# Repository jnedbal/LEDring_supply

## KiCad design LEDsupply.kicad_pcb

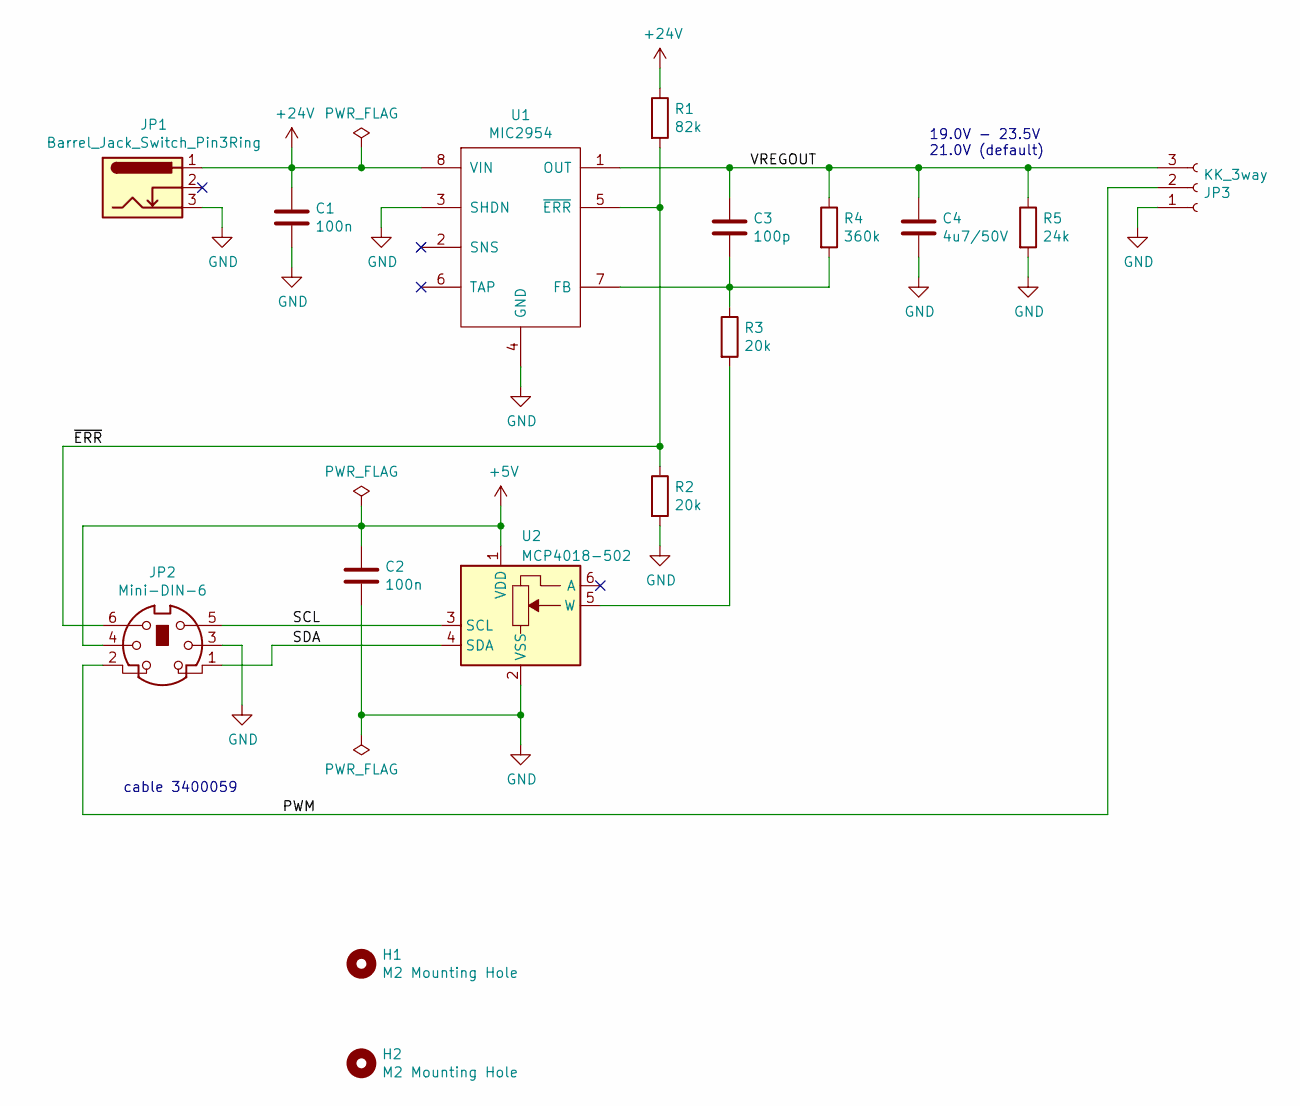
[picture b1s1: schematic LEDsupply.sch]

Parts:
C1, C2: 100n; C_0603_1608Metric; Part Number MC0603B104K500CT
C3: 100p; C_0603_1608Metric; Part Number MC0603B101K500CT
C4: 4u7/50V; C_1206_3216Metric; Part Number GRM31CR71H475KA12L
H1, H2: M2 Mounting Hole; MountingHole_2.2mm_M2
JP1: Barrel_Jack_Switch_Pin3Ring; 2.1mmBarrelJackTop; Part Number FC681473
JP2: Mini-DIN-6; MiniDIN6way; Part Number PSG01567
JP3: KK_3way; Molex_KK-254_AE-6410-03A_1x03_P2.54mm_Vertical; Part Number 22-27-2031
R1: 82k; R_0603_1608Metric; Part Number MCWR06X8202FTL
R2, R3: 20k; R_0603_1608Metric; Part Number MCWR06X2002FTL
R4: 360k; R_0603_1608Metric; Part Number MCWR06X3603FTL
R5: 24k; R_0603_1608Metric; Part Number MCWR06X2402FTL
U1: MIC2954; SO-8_3.9x4.9mm_P1.27mm; Part Number MIC2954-08YM
U2: MCP4018-502; SOT-363_SC-70-6; Part Number MCP4018T-502E/LT

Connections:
+5V: C2.1, JP2.4, U2.1 (VDD)
+24V: C1.1, JP1.1, R1.1, U1.8 (VIN)
/PWM: JP2.2, JP3.2
/SCL: JP2.5, U2.3 (SCL)
/SDA: JP2.1, U2.4 (SDA)
/VREGOUT: C3.1, C4.1, JP3.3, R4.1, R5.1, U1.1 (OUT)
/~ERR: JP2.6, R1.2, R2.1, U1.5 (~ERR)
GND: C1.2, C2.2, C4.2, JP1.3, JP2.3, JP3.1, R2.2, R5.2, U1.3 (SHDN), U1.4 (GND), U2.2 (VSS)
unnamed: C3.2, R3.1, R4.2, U1.7 (FB)
unnamed: R3.2, U2.5 (W)

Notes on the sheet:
19.0V - 23.5V 21.0V (default)
cable 3400059

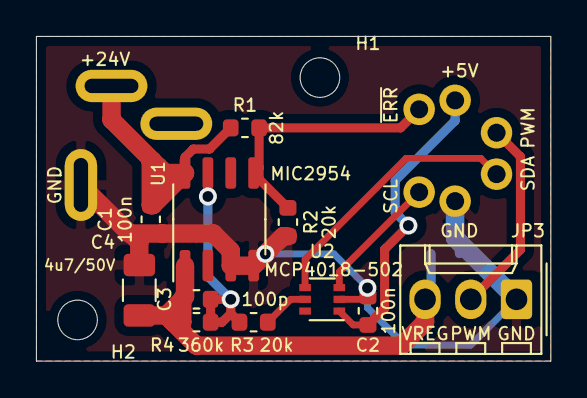
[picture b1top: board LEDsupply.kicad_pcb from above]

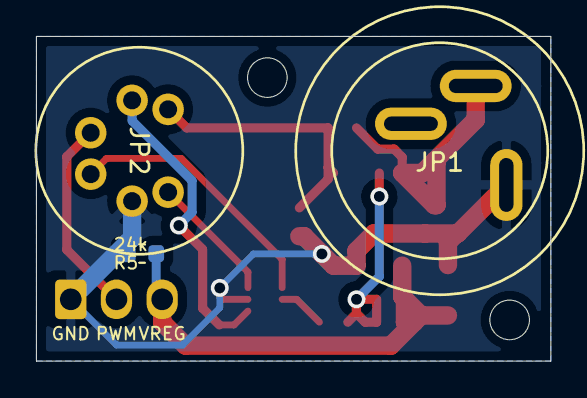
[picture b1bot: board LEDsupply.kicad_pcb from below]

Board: 2 copper layers, 28.6 x 18.0 mm, 16 parts (3 on the bottom side), 10 nets.

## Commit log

2020-12-04 Added a KK series connector
2021-01-12 Added I2C pullup resistors, fixed H1 label position, changed R4 from 20 to 24k
2021-01-12 Updated board zip file
